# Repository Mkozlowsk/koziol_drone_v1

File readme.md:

# STM32F411 FPV Drone
In progress..

## Project Description
Hobby FPV drone basing on a STM32F411vet6 uC. Still in progress.

### Features
- Flight controller with a gyroscope, accelerometer, magnetometer, compass, barometer and gps.
- PC FPV reciever
- 4 BLDC rotors drived by ESCs

### Technologies and Tools
- **C**
- **KiCad**  
- **CubeIDE**
- **STM32F411**

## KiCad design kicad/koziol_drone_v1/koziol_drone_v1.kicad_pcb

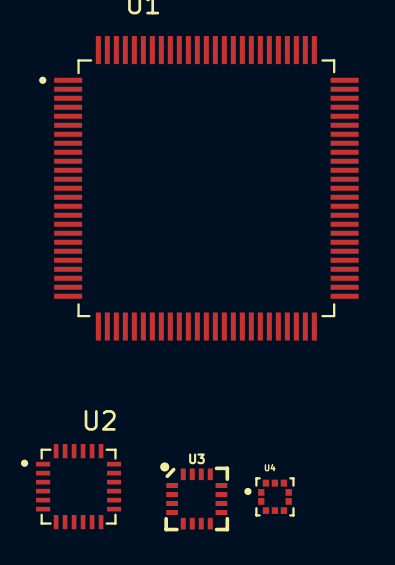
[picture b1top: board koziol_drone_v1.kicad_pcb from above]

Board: 2 copper layers, 4 parts (0 on the bottom side), 4 nets, no tracks yet.

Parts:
U1: STM32F411VET6
U2: MPU-6050
U3: HMC5883L
U4: BMP388

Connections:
+3.3V: U2.8 (VLOGIC), U2.13 (VDD), U3.2 (VDD), U3.4 (S1), U3.13 (VDDIO), U4.1 (VDDIO), U4.6 (CSB), U4.10 (VDD)
GND: U2.1 (CLKIN), U2.18 (GND), U3.9 (GND@1), U3.11 (GND@2), U4.3 (VSS), U4.5 (SDO), U4.8 (VSS), U4.9 (VSS)
unnamed: U1.11 (VDD), U1.19 (VDD), U1.28 (VDD), U1.50 (VDD), U1.75 (VDD), U1.100 (VDD)
unnamed: U1.10 (VSS), U1.27 (VSS), U1.49 (VSS), U1.74 (VSS), U1.99 (VSS)

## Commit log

2024-03-11 init
2024-03-11 template
2024-03-11 kicad init
2024-03-11 schemes progress
2024-03-11 mcu scheme + buses
2024-12-25 Update readme.md
    README UPDATE
2024-12-27 scheme descriptions and PDF plot
